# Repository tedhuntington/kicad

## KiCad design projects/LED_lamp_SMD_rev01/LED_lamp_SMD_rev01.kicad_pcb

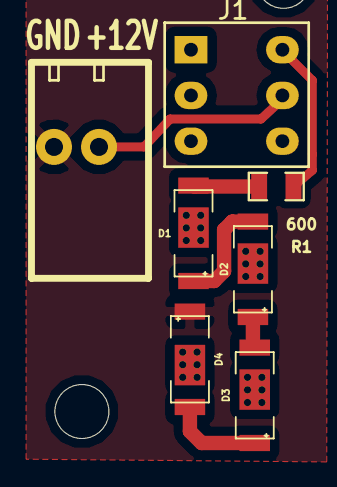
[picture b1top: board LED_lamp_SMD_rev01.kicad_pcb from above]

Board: 2 copper layers, 9 parts (0 on the bottom side), 7 nets.

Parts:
D1, D2, D3, D4: LED; TED_SM5730_LED
H1, H2: HOLE; TED_Hole_3mm
J1: DPDT_Switch; TED_SWITCHx3
J3: TERMINAL_2X1; TED_TERMINAL_SPRING_2.54MM_2PIN_1989748
R1: 600; TED_SM0805_R

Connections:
12V: J1.4, J3.1
GND: D4.2, J3.2
unnamed: D1.1, R1.1
unnamed: D1.2, D2.1
unnamed: D2.2, D3.1
unnamed: D3.2, D4.1
unnamed: J1.2, R1.2

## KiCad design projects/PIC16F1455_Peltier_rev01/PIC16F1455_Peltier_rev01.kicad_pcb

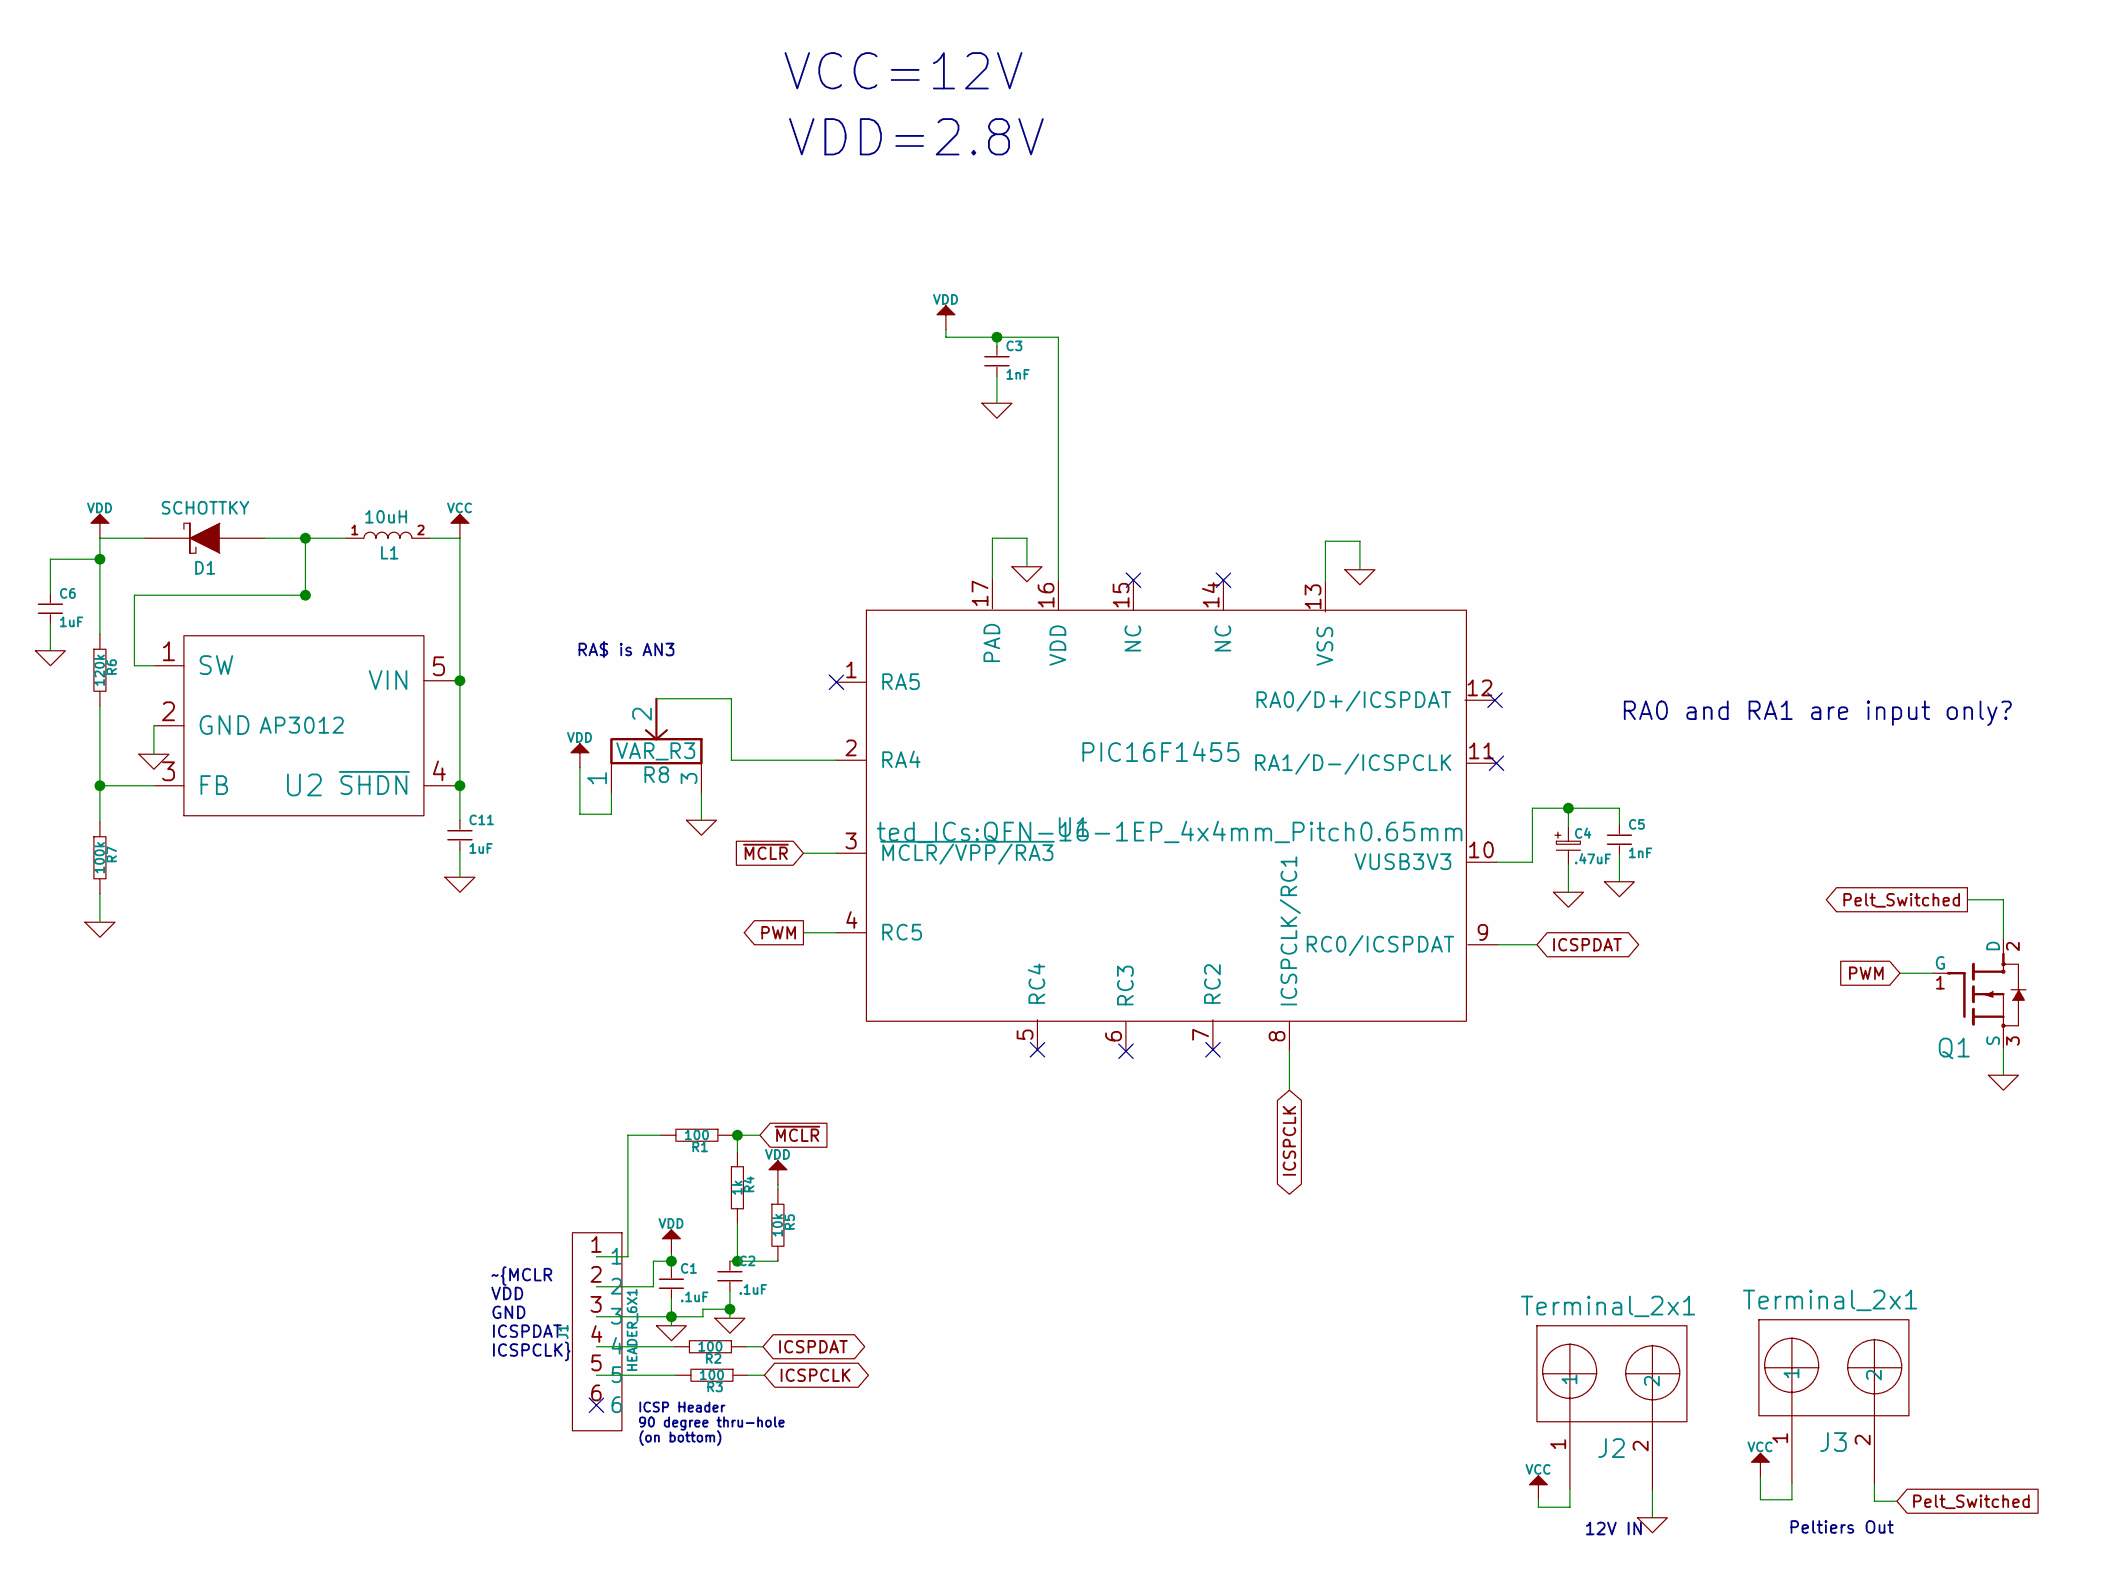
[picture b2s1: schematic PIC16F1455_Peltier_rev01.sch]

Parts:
C1, C2: .1uF; TED_SM0603_C
C3, C5: 1nF; TED_SM0603_C
C4: .47uF; TED_SM2012_0805_ELEC_C
C6, C11: 1uF; TED_SM0603_C
D1: SCHOTTKY; TED_DO-214AC
J1: HEADER_6X1; TED_HEADER_6x1
J2, J3: Terminal_2x1; TED_TERMINAL_3.5MM_2PIN
L1: 10uH; TED_SM0603_R
Q1: NMOSFET_GDS; TO-220_Neutral123_Vertical_LargePads
R1, R2, R3: 100; TED_SM0603_R
R4: 1k; TED_SM0603_R
R5: 10k; TED_SM0603_R
R6: 120k; TED_SM0603_R
R7: 100k; TED_SM0603_R
R8: VAR_R3; TED_PVZ3A
U1: PIC16F1455; QFN-16-1EP_4x4mm_Pitch0.65mm
U2: AP3012; TED_SOT-23-5

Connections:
GND: C1.2, C2.2, C3.2, C4.2, C5.2, C6.2, C11.2, J1.3, J2.2, Q1.3 (S), R7.2, R8.3, U1.13 (VSS), U1.17 (PAD), U2.2 (GND)
ICSPCLK: R3.1, U1.8 (ICSPCLK/RC1)
ICSPDAT: R2.1, U1.9 (RC0/ICSPDAT)
unnamed: C2.1, R4.2, R5.2
unnamed: C4.1, C5.1, U1.10 (VUSB3V3)
unnamed: D1.2 (A), L1.1, U2.1 (SW)
unnamed: J1.1, R1.2
unnamed: J1.4, R2.2
unnamed: J1.5, R3.2
unnamed: R6.2, R7.1, U2.3 (FB)
unnamed: R8.2, U1.2 (RA4)
PWM: Q1.1 (G), U1.4 (RC5)
Pelt_Switched: J3.2, Q1.2 (D)
VCC: C11.1, J2.1, J3.1, L1.2, U2.4 (~SHDN), U2.5 (VIN)
VDD: C1.1, C3.1, C6.1, D1.1 (K), J1.2, R5.1, R6.1, R8.1, U1.16 (VDD)
~MCLR~: R1.1, R4.1, U1.3 (~MCLR/VPP/RA3)

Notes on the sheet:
ICSP Header 90 degree thru-hole (on bottom)
VDD=2.8V
RA0 and RA1 are input only?
VCC=12V
12V IN
RA$ is AN3
Peltiers Out
~MCLR VDD GND ICSPDAT ICSPCLK

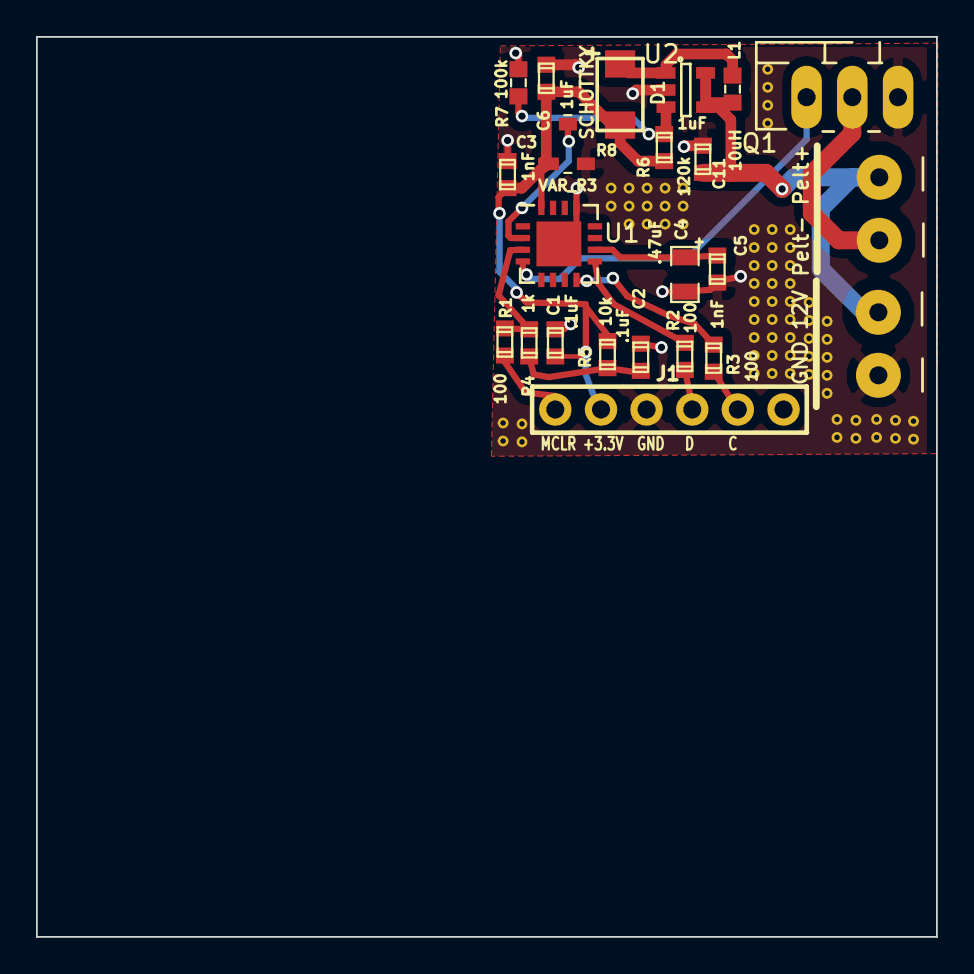
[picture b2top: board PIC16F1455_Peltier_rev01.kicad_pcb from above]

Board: 2 copper layers, 50.0 x 50.0 mm, 23 parts (0 on the bottom side), 16 nets.

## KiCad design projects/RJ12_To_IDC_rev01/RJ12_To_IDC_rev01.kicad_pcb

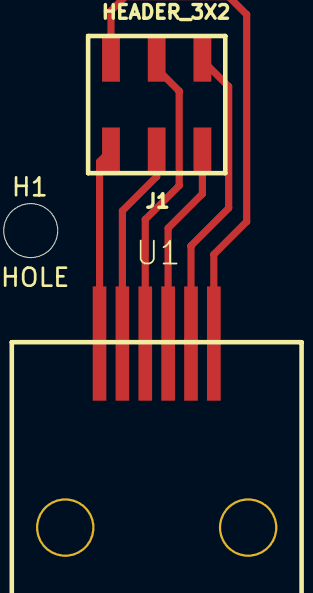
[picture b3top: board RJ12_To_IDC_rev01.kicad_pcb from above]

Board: 2 copper layers, 3 parts (0 on the bottom side), 6 nets.

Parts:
H1: HOLE; TED_Hole_3mm
J1: HEADER_3X2; TED_HEADER_3x2_SMT
U1: RJ12; TED_RJ12_955016669

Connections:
CS: J1.4, U1.2
GND: J1.6, U1.1
MODE: J1.2, U1.5
PHASE: J1.5, U1.4
PWM: J1.3, U1.3
VDD: J1.1, U1.6

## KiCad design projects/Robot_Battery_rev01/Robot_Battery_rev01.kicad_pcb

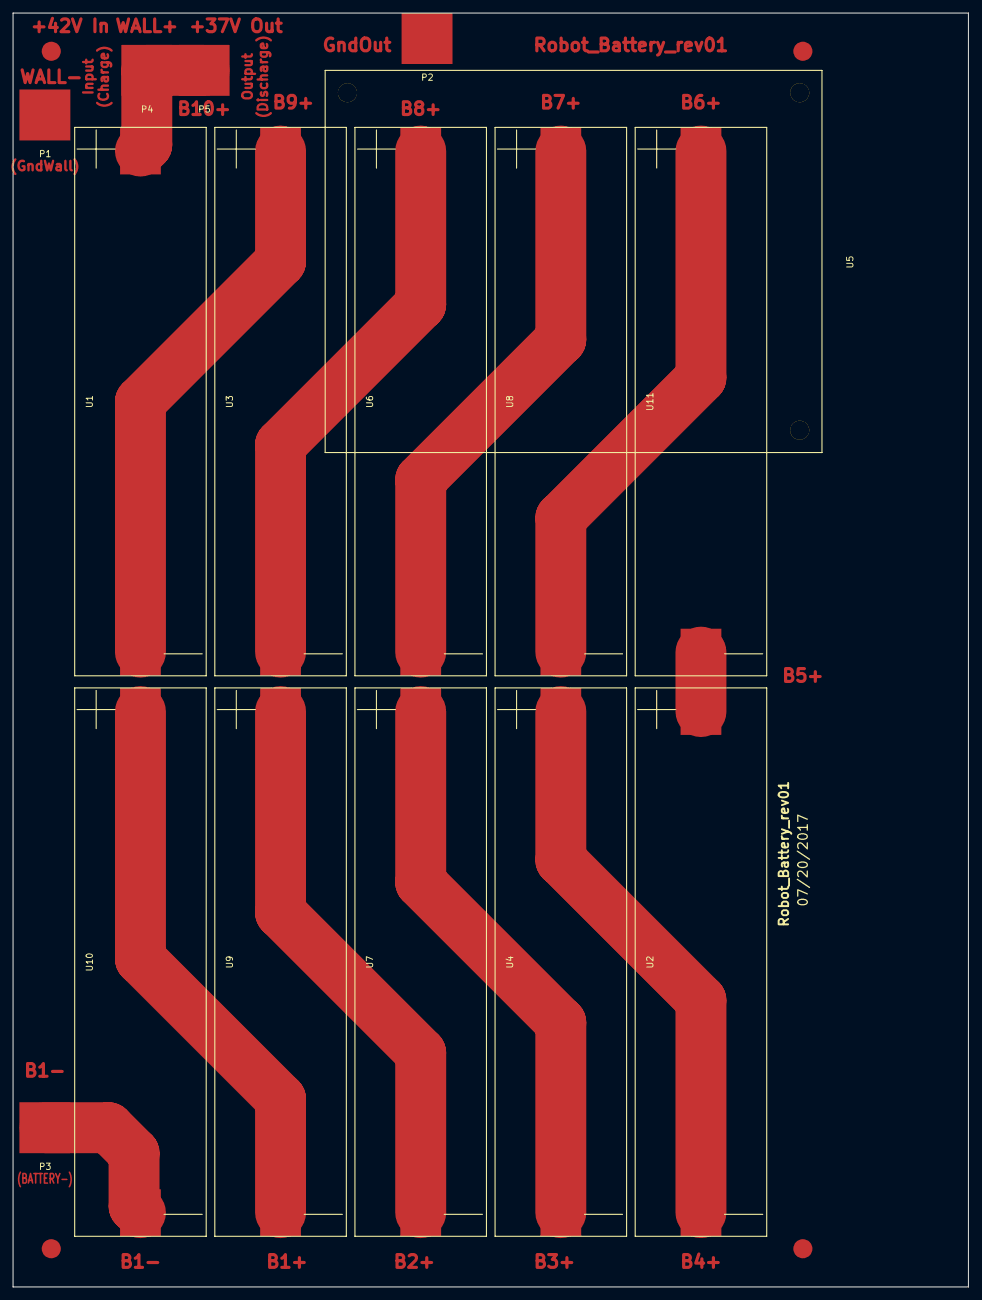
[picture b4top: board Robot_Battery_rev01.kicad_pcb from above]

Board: 2 copper layers, 150.0 x 200.0 mm, 20 parts (0 on the bottom side), 11 nets.

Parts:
H1, H2, H3, H4: HOLE; TED_Hole_3mm
P1: GND_WALL; SolderPad
P2: GND_OUT; SolderPad
P3: BATTERY-; SolderPad
P4: VWall; SolderPad
P5: VOut; SolderPad
U1, U2, U3, U4, U6, U7, U8, U9, U10, U11: BatteryHolder_18650_1x1; 18650_Battery_Holder_SMD
U5: Battery_Charger_10S; Battery_Charger_LH_HP145A

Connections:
B1+: U9.2, U10.1
B1-: P3.1, U10.2
B2+: U7.2, U9.1
B3+: U4.2, U7.1
B4+: U2.2, U4.1
B5+: U2.1, U11.2
B6+: U8.2, U11.1
B7+: U6.2, U8.1
B8+: U3.2, U6.1
B9+: U1.2, U3.1
B10+: P4.1, P5.1, U1.1
